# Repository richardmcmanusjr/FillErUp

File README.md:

# FillErUp
Senior Design Project - Class of 2024

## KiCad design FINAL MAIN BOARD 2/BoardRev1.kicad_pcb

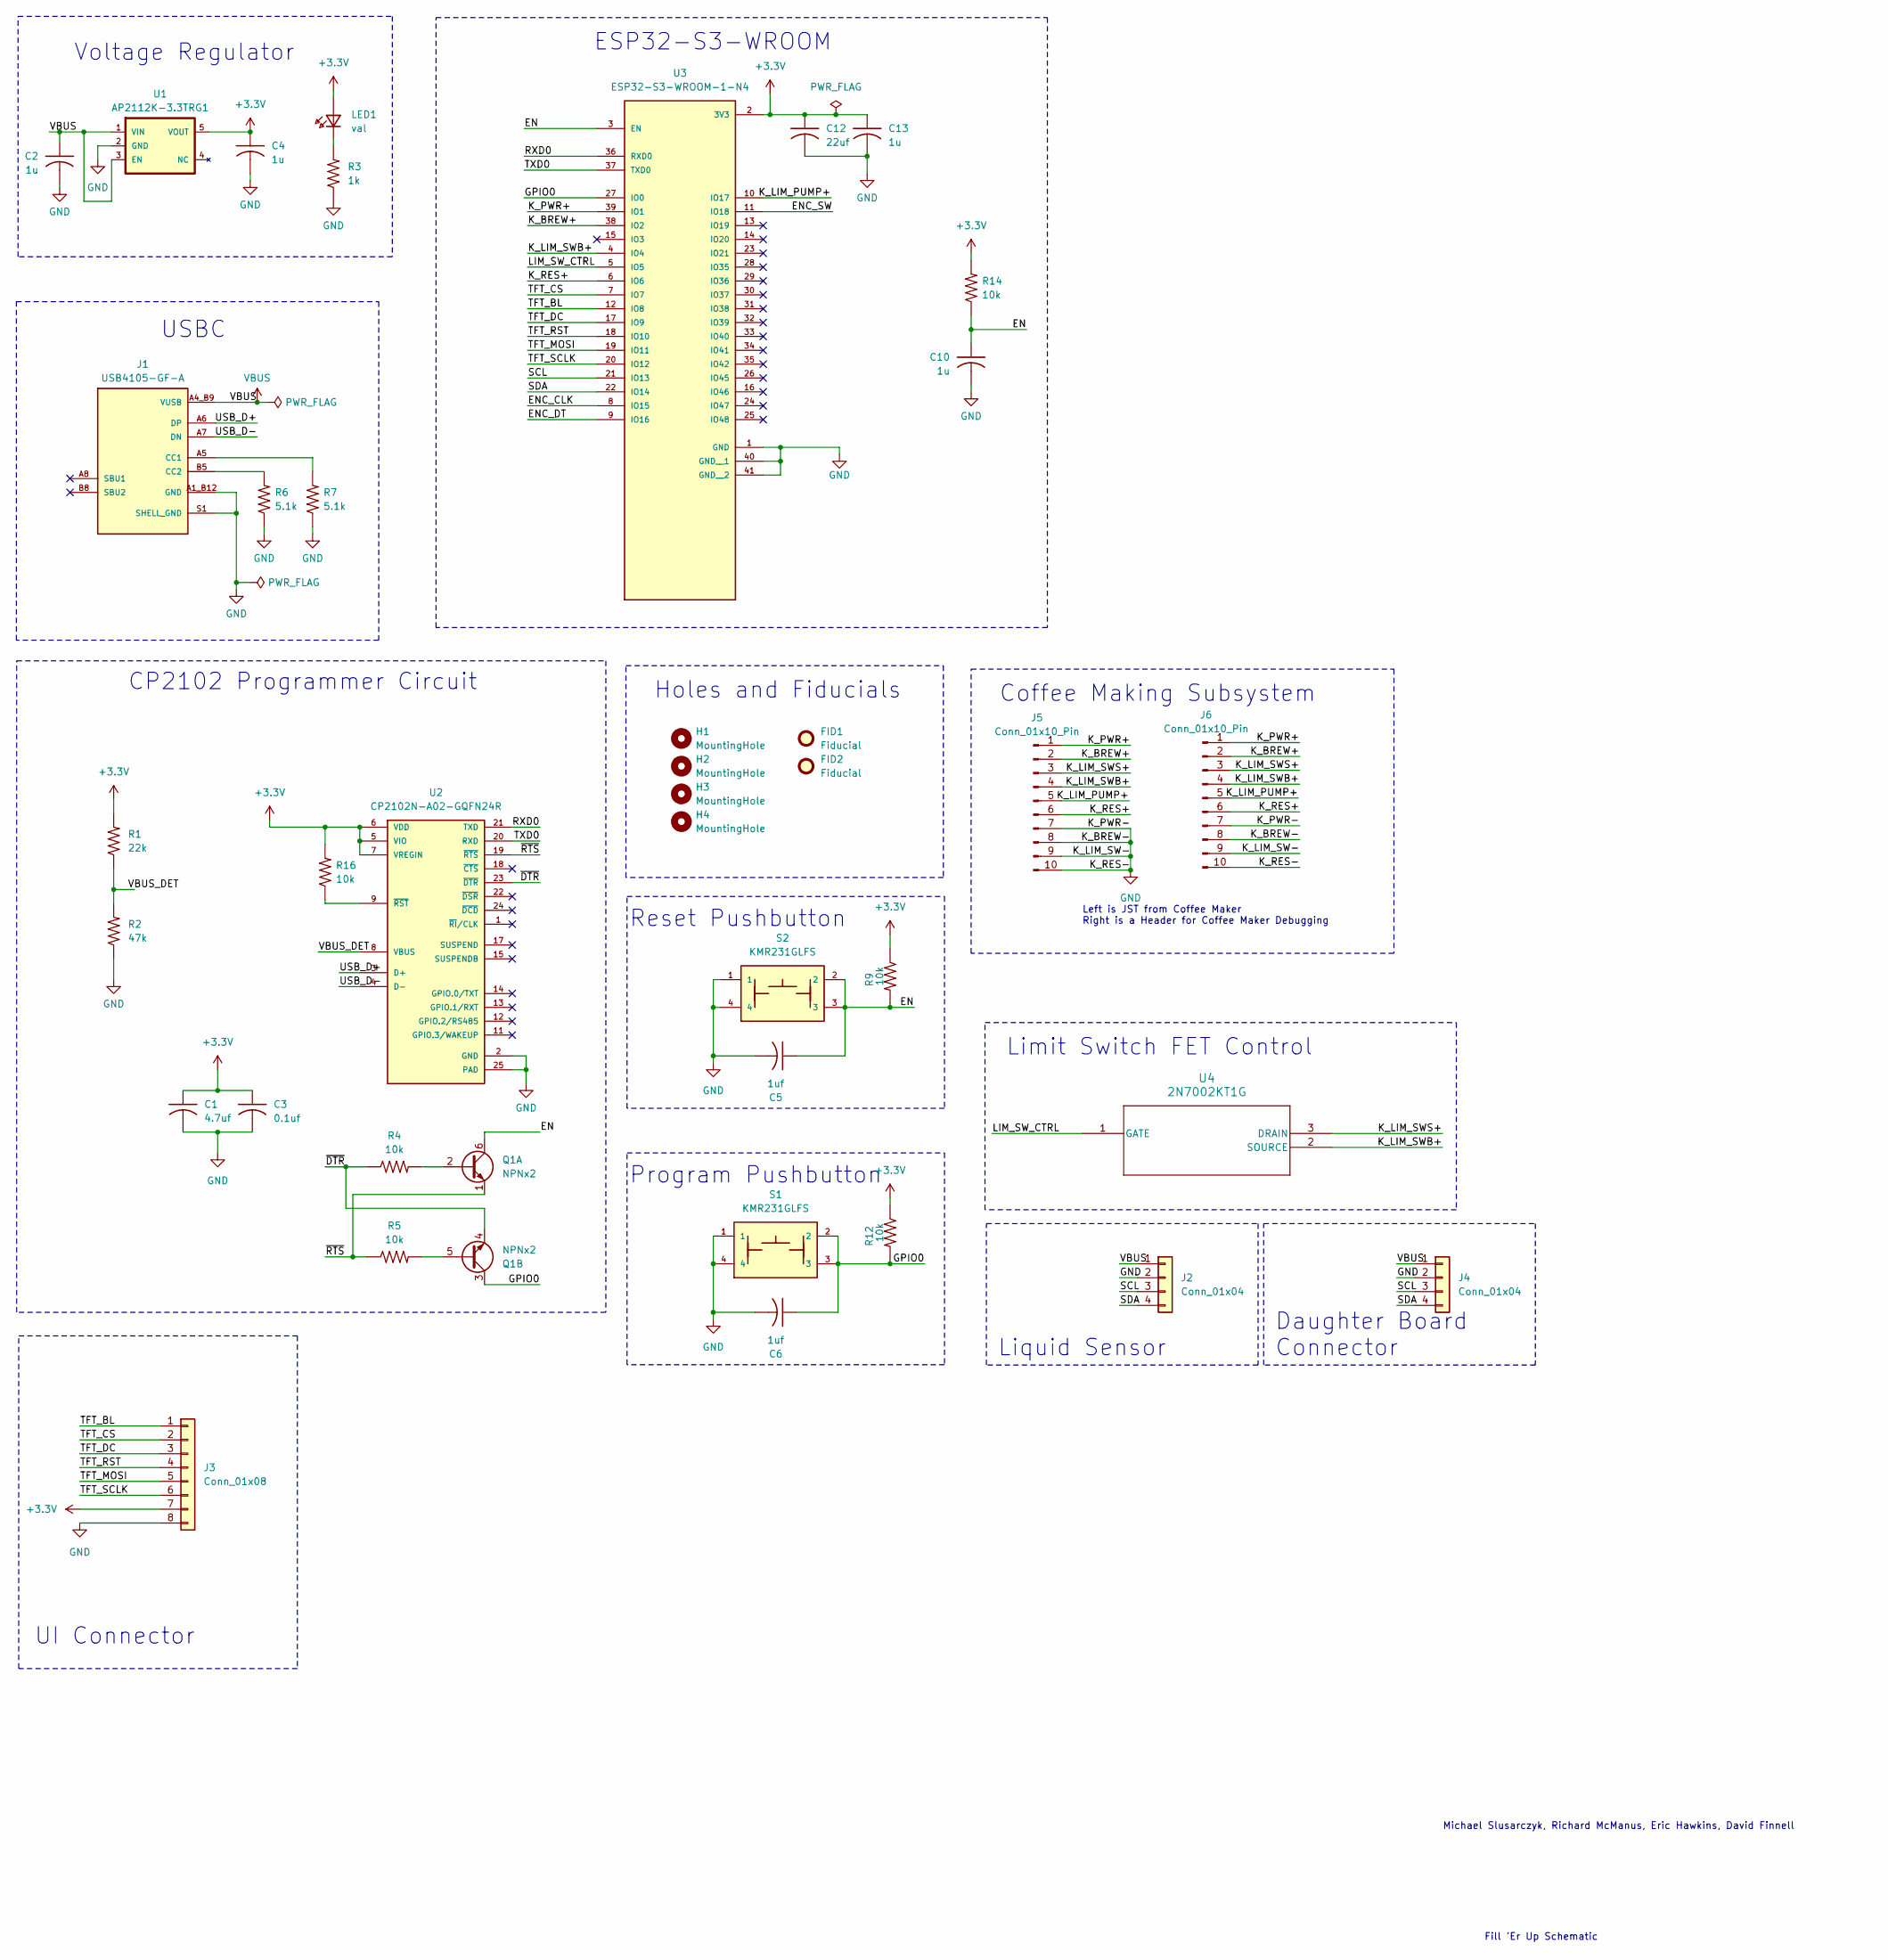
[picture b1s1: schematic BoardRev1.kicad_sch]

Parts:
C1: 4.7uf; C0603
C2, C4, C10, C13: 1u; C0603
C3: 0.1uf; C0603
C5, C6: 1uf; C0603
C12: 22uf; C0805
FID1, FID2: Fiducial; Fiducial_1mm_Mask3mm
H1, H2, H3, H4: MountingHole; mounting_hole
J1: USB4105-GF-A; GCT4105; PARTREV A3
J2, J4: Conn_01x04; JST_XH_S4B-XH-A_1x04_P2.50mm_Horizontal
J3: Conn_01x08; JST_XH_S8B-XH-A_1x08_P2.50mm_Horizontal
J5: Conn_01x10_Pin; JST_XH_S10B-XH-A-1_1x10_P2.50mm_Horizontal
J6: Conn_01x10_Pin; PinHeader_1x10_P2.54mm_Vertical
LED1: val; LED_0603
Q1: NPNx2; SC70-6
R1: 22k; C0603
R2: 47k; C0603
R3: 1k; C0603
R4, R5, R9, R12, R14, R16: 10k; C0603
R6, R7: 5.1k; C0603
S1, S2: KMR231GLFS; PB4X2
U1: AP2112K-3.3TRG1; SOT25; PARTREV 2-2
U2: CP2102N-A02-GQFN24R; QFN-24
U3: ESP32-S3-WROOM-1-N4; ESP32-S3-Wroom-1; PARTREV v1.0
U4: 2N7002KT1G; SOT-23_ONS

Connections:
+3.3V: C1.1, C3.1, C4.1, C12.1, C13.1, J3.7, LED1.2 (A), R1.2, R9.1, R12.1, R14.2, R16.2, U1.5 (VOUT), U2.5 (VIO), U2.6 (VDD), U2.7 (VREGIN), U3.2 (3V3)
/EN: C5.1, C10.1, Q1.6 (C1), R9.2, R14.1, S2.2, S2.3, U3.3 (EN)
/ENC_CLK: U3.8 (IO15)
/ENC_DT: U3.9 (IO16)
/ENC_SW: U3.11 (IO18)
/GPIO0: C6.1, Q1.3 (C2), R12.2, S1.2, S1.3, U3.27 (IO0)
/K_BREW+: J5.2, J6.2, U3.38 (IO2)
/K_LIM_PUMP+: J5.5, J6.5, U3.10 (IO17)
/K_LIM_SWB+: J5.4, J6.4, U3.4 (IO4), U4.2 (SOURCE)
/K_LIM_SWS+: J5.3, J6.3, U4.3 (DRAIN)
/K_PWR+: J5.1, J6.1, U3.39 (IO1)
/K_RES+: J5.6, J6.6, U3.6 (IO6)
/LIM_SW_CTRL: U3.5 (IO5), U4.1 (GATE)
/RXD0: U2.21 (TXD), U3.36 (RXD0)
/SCL: J2.3, J4.3, U3.21 (IO13)
/SDA: J2.4, J4.4, U3.22 (IO14)
/TFT_BL: J3.1, U3.12 (IO8)
/TFT_CS: J3.2, U3.7 (IO7)
/TFT_DC: J3.3, U3.17 (IO9)
/TFT_MOSI: J3.5, U3.19 (IO11)
/TFT_RST: J3.4, U3.18 (IO10)
/TFT_SCLK: J3.6, U3.20 (IO12)
/TXD0: U2.20 (RXD), U3.37 (TXD0)
/USB_D+: J1.A6 (DP), J1.B6 (DP), U2.3 (D+)
/USB_D-: J1.A7 (DN), J1.B7 (DN), U2.4 (D-)
/VBUS_DET: R1.1, R2.2, U2.8 (VBUS)
/~DTR: Q1.4 (E2), R4.1, U2.23 (~DTR)
/~RTS: Q1.1 (E1), R5.1, U2.19 (~RTS)
GND: C1.2, C2.2, C3.2, C4.2, C5.2, C6.2, C10.2, C12.2, C13.2, J1.A1_B12 (GND), J1.B1_A12 (GND), J1.S1 (SHELL_GND), J1.S2 (SHELL_GND), J1.S3 (SHELL_GND), J1.S4 (SHELL_GND), J2.2, J3.8, J4.2, J5.7, J5.8, J5.9, J5.10, J6.7, J6.8, J6.9, J6.10, R2.1, R3.1, R6.1, R7.1, S1.1, S1.4, S2.1, S2.4, U1.2 (GND), U2.2 (GND), U2.25 (PAD), U3.1 (GND), U3.40 (GND__1), U3.41 (GND__2)
unnamed: J1.A5 (CC1), R7.2
unnamed: J1.B5 (CC2), R6.2
unnamed: LED1.1 (C), R3.2
unnamed: Q1.2 (B1), R4.2
unnamed: Q1.5 (B2), R5.2
unnamed: R16.1, U2.9 (~RST)
VUSB: C2.1, J1.A4_B9 (VUSB), J1.B4_A9 (VUSB), J2.1, J4.1, U1.1 (VIN), U1.3 (EN)

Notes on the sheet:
Fill 'Er Up Schematic
UI Connector
Limit Switch FET Control
Liquid Sensor
Coffee Making Subsystem
Holes and Fiducials
Reset Pushbutton
Program Pushbutton
CP2102 Programmer Circuit
USBC
Left is JST from Coffee Maker Right is a Header for Coffee Maker Debugging
Daughter Board Connector
Voltage Regulator
ESP32-S3-WROOM
Michael Slusarczyk, Richard McManus, Eric Hawkins, David Finnell

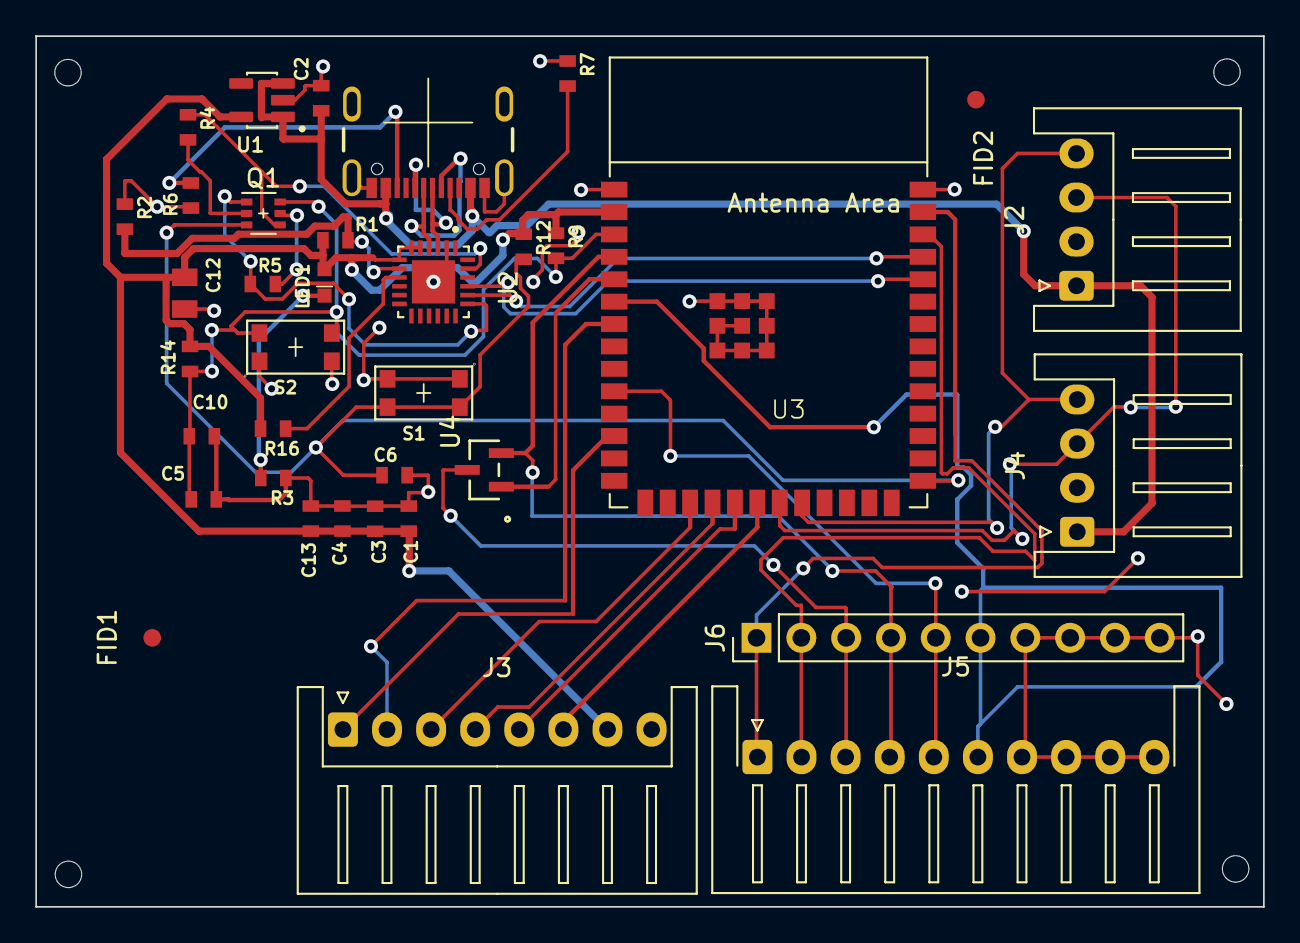
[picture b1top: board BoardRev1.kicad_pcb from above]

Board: 2 copper layers, 69.6 x 49.4 mm, 40 parts (0 on the bottom side), 33 nets.

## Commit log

2024-01-30 Organized two teams
2024-01-30 Added Eric's Video
2024-03-07 Started Preliminary Board Design
2024-04-03 Added Brew Cycle Code
2024-04-17 Added Latest
2024-04-19 Added Files
2024-04-20 Added File
2024-04-20 Removed
2024-04-22 Added working code
2024-04-29 Added
